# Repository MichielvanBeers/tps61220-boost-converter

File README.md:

Repository for an example breakout board for the TPS61220 boost converter IC from Texas Instruments.

This repository contains the schematic and PCB layout files for a simple breakout board designed to make it easy to use the TPS61220 in your projects. The TPS61220 is a high-efficiency boost converter capable of stepping up low input voltages to higher output voltages, making it ideal for battery-powered applications.

This breakout board is modelled after the TPS61220EVM-319 evaluation module (link below).

## Example Images

## Usage
If R1 is set to 1Mohms and R2 is set to 180kohms, the output voltage will be 3.28V when powered from a < 3.28V source.

## Contents
- Schematic files
- PCB layout files

## Bill of Materials (BOM)

This BOM lists the components used in the associated design.

| Line No. | Manufacturer Part No. | Description | Manufacturer | Quantity | Mouser Part Number |
|:---:|:---:|:---|:---|:---:|:---:|
| 1 | TPS61220DCKR | Tiny Low Inp Vltg Bo / Schakelende spanningsregelaars | Texas Instruments | 1 | 595-TPS61220DCKR |
| 2 | EPL3015-472MLC | 4.7uH Shld 20% 1.4A / Vermogensinductoren - SMD | Coilcraft | 1 | 994-EPL3015-472MLC |
| 3 | GRM188R60J106ME47J | 10 uF 6.3 VDC 20% 06 / Meerlaagse keramische condensatoren MLCC - SMD/SMT | Murata Electronics | 2 | 81-GRM188R60J106ME7J |

---

### Notes
* Quantity refers to the "Besteld Aantal Quantity Ordered" from the source document, which is the total count of components required for the order or project.
* The Manufacturer Part Number and Description are key identifiers for the component.
* The Mouser Part Number is included for easy reference and reordering.

## Relevant Links

- [TPS61220 Product Page](https://www.ti.com/product/TPS61220)
- [TPS61220EVM-319 Evaluation Module](https://www.ti.com/tool/TPS61220EVM-319)
- [EEVBlog post with debug help](https://www.eevblog.com/forum/beginners/kindly-requesting-help-with-debugging-a-tsp61220-(pcb)-voltage-boost-converter/)

## License
This project is licensed under the MIT License - see the [LICENSE](LICENSE) file for details.

## Acknowledgments
User from the EEVBlog forum for assistance with debugging the design:
- tooki
- mdijkens
- Psi
- ahsrabrifat
- MariuszD
- Slh
- xvr
- MathWizard

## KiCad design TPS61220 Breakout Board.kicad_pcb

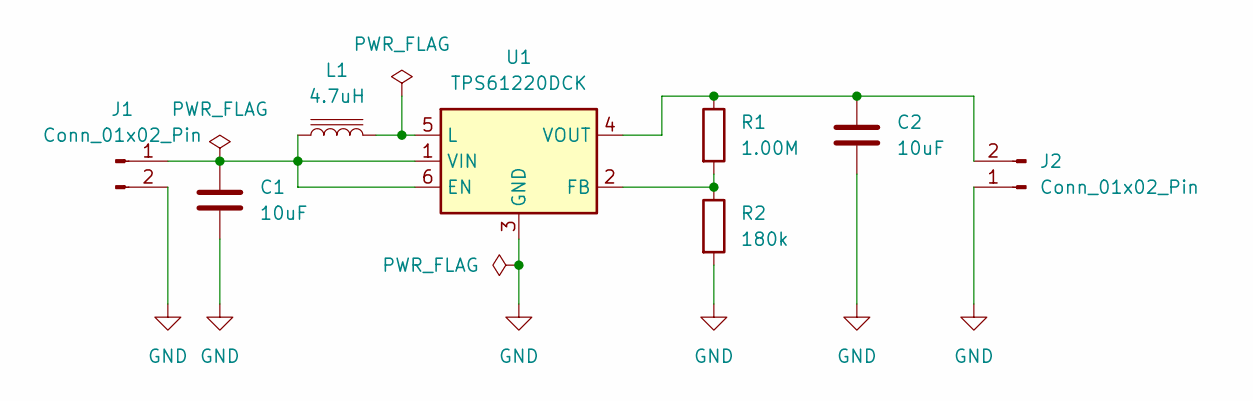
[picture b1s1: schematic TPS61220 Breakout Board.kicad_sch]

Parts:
C1, C2: 10uF; C_0603_1608Metric_Pad1.08x0.95mm_HandSolder
J1, J2: Conn_01x02_Pin; PinHeader_1x02_P2.54mm_Vertical
L1: 4.7uH; EPL3015472MLC
R1: 1.00M; C_1206_3216Metric_Pad1.33x1.80mm_HandSolder
R2: 180k; C_1206_3216Metric_Pad1.33x1.80mm_HandSolder
U1: TPS61220DCK; Texas_R-PDSO-G6

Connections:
GND: C1.2, C2.2, J1.2 (GND), J2.1 (GND), R2.2, U1.3 (GND)
unnamed: C1.1, J1.1 (VIN), L1.1, U1.1 (VIN), U1.6 (EN)
unnamed: C2.1, J2.2 (VOUT), R1.1, U1.4 (VOUT)
unnamed: R1.2, R2.1, U1.2 (FB)
unnamed: L1.2, U1.5 (L)

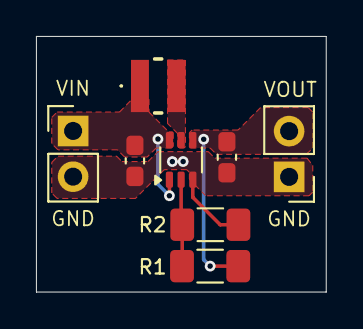
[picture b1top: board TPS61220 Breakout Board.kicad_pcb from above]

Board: 2 copper layers, 16.1 x 14.2 mm, 8 parts (0 on the bottom side), 5 nets.

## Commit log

2025-10-22 Add BOM and image
2025-10-22 Add PCB images and constrain height
2025-10-22 Use HTML to constrain image on Github
